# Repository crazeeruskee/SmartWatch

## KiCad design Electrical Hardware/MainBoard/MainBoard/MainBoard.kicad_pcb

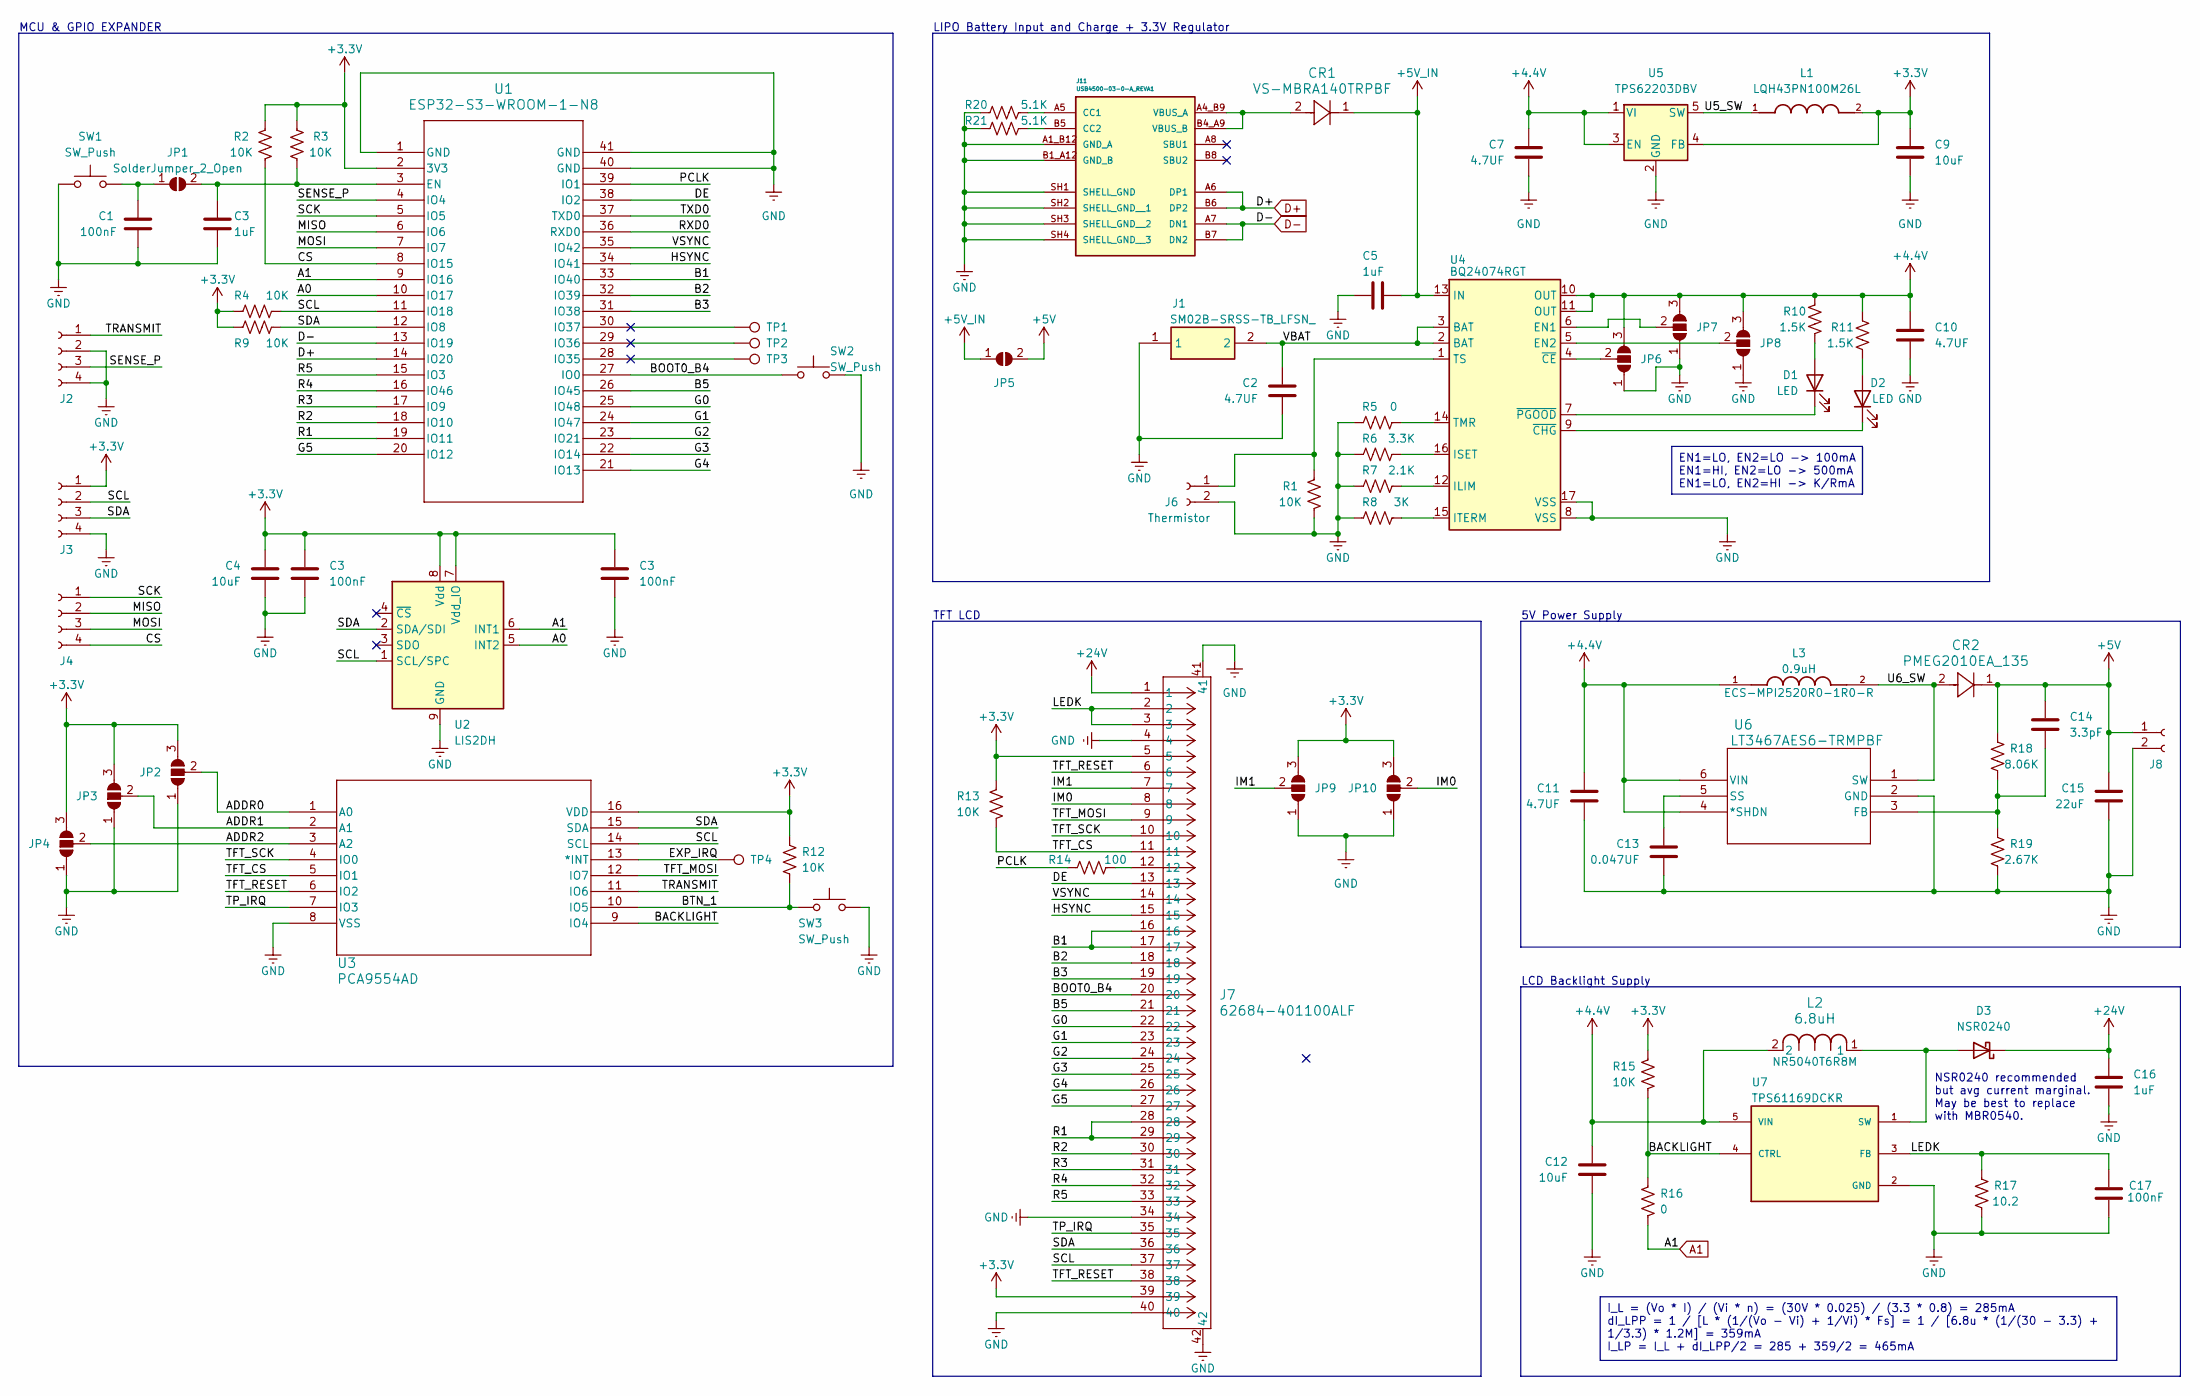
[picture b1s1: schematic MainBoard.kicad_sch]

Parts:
C1, C17: 100nF; C_0603_1608Metric
C2, C7, C10, C11: 4.7UF; C_0603_1608Metric
C3, C5, C16: 1uF; C_0603_1608Metric
C4, C9, C12: 10uF; C_0805_2012Metric
C13: 0.047UF; C_0603_1608Metric
C14: 3.3pF; C_0603_1608Metric
C15: 22uF; C_0805_2012Metric
CR1: VS-MBRA140TRPBF; DIODE_SMA_VIS-L
CR2: PMEG2010EA_135; CR_PMEG2010_NEX
D1, D2: LED; LED_0603_1608Metric
D3: NSR0240; D_SOD-123
J1: SM02B-SRSS-TB_LFSN_; SM02B-SRSS-TB; Manufacturer_Part_Number SM02B-SRSS-TB(LFSN)
J2, J3, J4: Conn_01x04_Socket; PinSocket_1x04_P1.00mm_Vertical
J6: Thermistor; PinSocket_1x02_P1.00mm_Vertical
J7: 62684-401100ALF; CONN40_1100ALF_AMP
J8: Conn_01x02_Socket; PinSocket_1x02_P1.00mm_Vertical
J11: USB4500-03-0-A_REVA1; GCT_USB4500-03-0-A_REVA1; PARTREV A1
JP1, JP5: SolderJumper_2_Open; SolderJumper-2_P1.3mm_Open_RoundedPad1.0x1.5mm
JP2, JP3, JP4, JP6, JP7, JP8, JP9, JP10: SolderJumper_3_Open; SolderJumper-3_P1.3mm_Open_RoundedPad1.0x1.5mm
L1: LQH43PN100M26L; IND_LQH43PN100M26L; PARTREV N/A
L2: 6.8uH; IND_TAIYO_NR5040_TAY; MPN NR5040T6R8M
L3: 0.9uH; IND_ECS-MPI2520R0-1R0-R; PARTREV B
R1, R2, R3, R4, R9, R12, R13, R15: 10K; R_0603_1608Metric
R5, R16: 0; R_0603_1608Metric
R6: 3.3K; R_0603_1608Metric
R7: 2.1K; R_0603_1608Metric
R8: 3K; R_0603_1608Metric
R10, R11: 1.5K; R_0603_1608Metric
R14: 100; R_0603_1608Metric
R17: 10.2; R_0603_1608Metric
R18: 8.06K; R_0603_1608Metric
R19: 2.67K; R_0603_1608Metric
R20, R21: 5.1K; R_0603_1608Metric
SW1, SW2, SW3: SW_Push; Panasonic_EVQPUJ_EVQPUA
TP1, TP2, TP3, TP4: TestPoint; TestPoint_Pad_D1.0mm
U1: ESP32-S3-WROOM-1-N8; ESP32-S3-WROOM-1-N8_EXP
U2: LIS2DH; LGA-14_2x2mm_P0.35mm_LayoutBorder3x4y
U3: PCA9554AD; SOT338-1_NXP-L
U4: BQ24074RGT; VQFN-16-1EP_3x3mm_P0.5mm_EP1.6x1.6mm
U5: TPS62203DBV; SOT-23-5
U6: LT3467AES6-TRMPBF; TSOT-23_S6_LIT
U7: TPS61169DCKR; SOT65P210X110-5N; PARTREV A

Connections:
+4V4: C7.1, C10.1, C11.1, C12.1, JP6.3 (B), JP7.3 (B), JP8.3 (B), L2.2, L3.1, R10.1, R11.2, U4.10 (OUT), U4.11 (OUT), U5.1 (VI), U5.3 (EN), U6.4 (*SHDN), U6.6 (VIN), U7.5 (VIN)
+5V: C14.1, C15.1, CR2.1, J8.1, JP5.2 (B), R18.1
+5V_IN: C5.1, CR1.1, JP5.1 (A), U4.13 (IN)
+24V: C16.1, D3.1 (K), J7.1
/A0: U1.10 (IO17), U2.5 (INT2)
/ADDR0: JP2.2 (C), U3.1 (A0)
/ADDR1: JP3.2 (C), U3.2 (A1)
/ADDR2: JP4.2 (C), U3.3 (A2)
/B1: J7.16, J7.17, U1.33 (IO40)
/B2: J7.18, U1.32 (IO39)
/B3: J7.19, U1.31 (IO38)
/B5: J7.21, U1.26 (IO45)
/BACKLIGHT: R15.2, R16.1, U3.9 (IO4), U7.4 (CTRL)
/BOOT0_B4: J7.20, SW2.1, U1.27 (IO0)
/BTN_1: R12.2, SW3.1, U3.10 (IO5)
/CS: J4.4, R2.2, U1.8 (IO15)
/DE: J7.13, U1.38 (IO2)
/EXP_IRQ: TP4.1, U3.13 (*INT)
/G0: J7.22, U1.25 (IO48)
/G1: J7.23, U1.24 (IO47)
/G2: J7.24, U1.23 (IO21)
/G3: J7.25, U1.22 (IO14)
/G4: J7.26, U1.21 (IO13)
/G5: J7.27, U1.20 (IO12)
/HSYNC: J7.15, U1.34 (IO41)
/IM0: J7.8, JP10.2 (C)
/IM1: J7.7, JP9.2 (C)
/LEDK: C17.1, J7.2, J7.3, R17.1, U7.3 (FB)
/MISO: J4.2, U1.6 (IO6)
/MOSI: J4.3, U1.7 (IO7)
/PCLK: R14.2, U1.39 (IO1)
/R1: J7.28, J7.29, U1.19 (IO11)
/R2: J7.30, U1.18 (IO10)
/R3: J7.31, U1.17 (IO9)
/R4: J7.32, U1.16 (IO46)
/R5: J7.33, U1.15 (IO3)
/RXD0: U1.36 (RXD0)
/SCK: J4.1, U1.5 (IO5)
/SCL: J3.2, J7.37, R4.2, U1.11 (IO18), U2.1 (SCL/SPC), U3.14 (SCL)
/SDA: J3.3, J7.36, R9.1, U1.12 (IO8), U2.2 (SDA/SDI), U3.15 (SDA)
/SENSE_P: J2.3, U1.4 (IO4)
/TFT_CS: J7.11, R13.2, U3.5 (IO1)
/TFT_MOSI: J7.9, U3.12 (IO7)
/TFT_RESET: J7.6, J7.38, U3.6 (IO2)
/TFT_SCK: J7.10, U3.4 (IO0)
/TP_IRQ: J7.35, U3.7 (IO3)
/TRANSMIT: J2.1, U3.11 (IO6)
/TXD0: U1.37 (TXD0)
/U5_SW: L1.1, U5.5 (SW)
/U6_SW: CR2.2, L3.2, U6.1 (SW)
/VBAT: C2.1, J1.2, U4.2 (BAT), U4.3 (BAT)
/VSYNC: J7.14, U1.35 (IO42)
A1: R16.2, U1.9 (IO16), U2.6 (INT1)
D+: J11.A6 (DP1), J11.B6 (DP2), U1.14 (IO20)
D-: J11.A7 (DN1), J11.B7 (DN2), U1.13 (IO19)
GND: C1.1, C2.2, C3.2, C4.2, C5.2, C7.2, C9.2, C10.2, C11.2, C12.2, C13.2, C15.2, C16.2, C17.2, J1.1, J2.2, J2.4, J3.4, J6.2, J7.4, J7.34, J7.40, J7.41, J7.42, J8.2, J11.A1_B12 (GND_A), J11.B1_A12 (GND_B), J11.SH1 (SHELL_GND), J11.SH2 (SHELL_GND__1), J11.SH3 (SHELL_GND__2), J11.SH4 (SHELL_GND__3), JP2.1 (A), JP3.1 (A), JP4.1 (A), JP6.1 (A), JP7.1 (A), JP8.1 (A), JP9.1 (A), JP10.1 (A), R1.2, R5.1, R6.1, R7.1, R8.1, R17.2, R19.2, R20.2, R21.2, SW1.1, SW2.2, SW3.2, U1.1 (GND), U1.40 (GND), U1.41 (GND), U2.9 (GND), U2.10 (GND), U2.11 (GND), U2.12 (GND), U2.13 (GND), U2.14 (GND), U3.8 (VSS), U4.8 (VSS), U4.17 (VSS), U5.2 (GND), U6.2 (GND), U7.2 (GND); also elsewhere on the board
unnamed: D1.2 (A), R10.2
unnamed: D1.1 (K), U4.7 (~PGOOD)
unnamed: D2.2 (A), R11.1
unnamed: D2.1 (K), U4.9 (~CHG)
unnamed: D3.2 (A), L2.1, U7.1 (SW)
unnamed: J6.1, R1.1, U4.1 (TS)
unnamed: J7.12, R14.1
unnamed: J11.A5 (CC1), R20.1
unnamed: J11.B5 (CC2), R21.1
unnamed: CR1.2, J11.A4_B9 (VBUS_A), J11.B4_A9 (VBUS_B)
unnamed: C1.2, JP1.1 (A), SW1.2
unnamed: JP6.2 (C), U4.4 (~CE)
unnamed: JP7.2 (C), U4.6 (EN1)
unnamed: JP8.2 (C), U4.5 (EN2)
unnamed: R7.2, U4.12 (ILIM)
unnamed: R6.2, U4.16 (ISET)
unnamed: R8.2, U4.15 (ITERM)
unnamed: R5.2, U4.14 (TMR)
unnamed: C14.2, R18.2, R19.1, U6.3 (FB)
unnamed: C13.1, U6.5 (SS)

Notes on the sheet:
I_L = (Vo * I) / (Vi * n) = (30V * 0.025) / (3.3 * 0.8) = 285mA dI_LPP = 1 / [L * (1/(Vo - Vi) + 1/Vi) * Fs] = 1 / [6.8u * (1/(30 - 3.3) + 1/3.3) * 1.2M] = 359mA I_LP = I_L + dI_LPP/2 = 285 + 359/2 = 465mA
EN1=LO, EN2=LO -> 100mA EN1=HI, EN2=LO -> 500mA EN1=LO, EN2=HI -> K/RmA
LCD Backlight Supply
5V Power Supply
LIPO Battery Input and Charge + 3.3V Regulator
MCU & GPIO EXPANDER
TFT LCD
NSR0240 recommended but avg current marginal. May be best to replace with MBR0540.

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
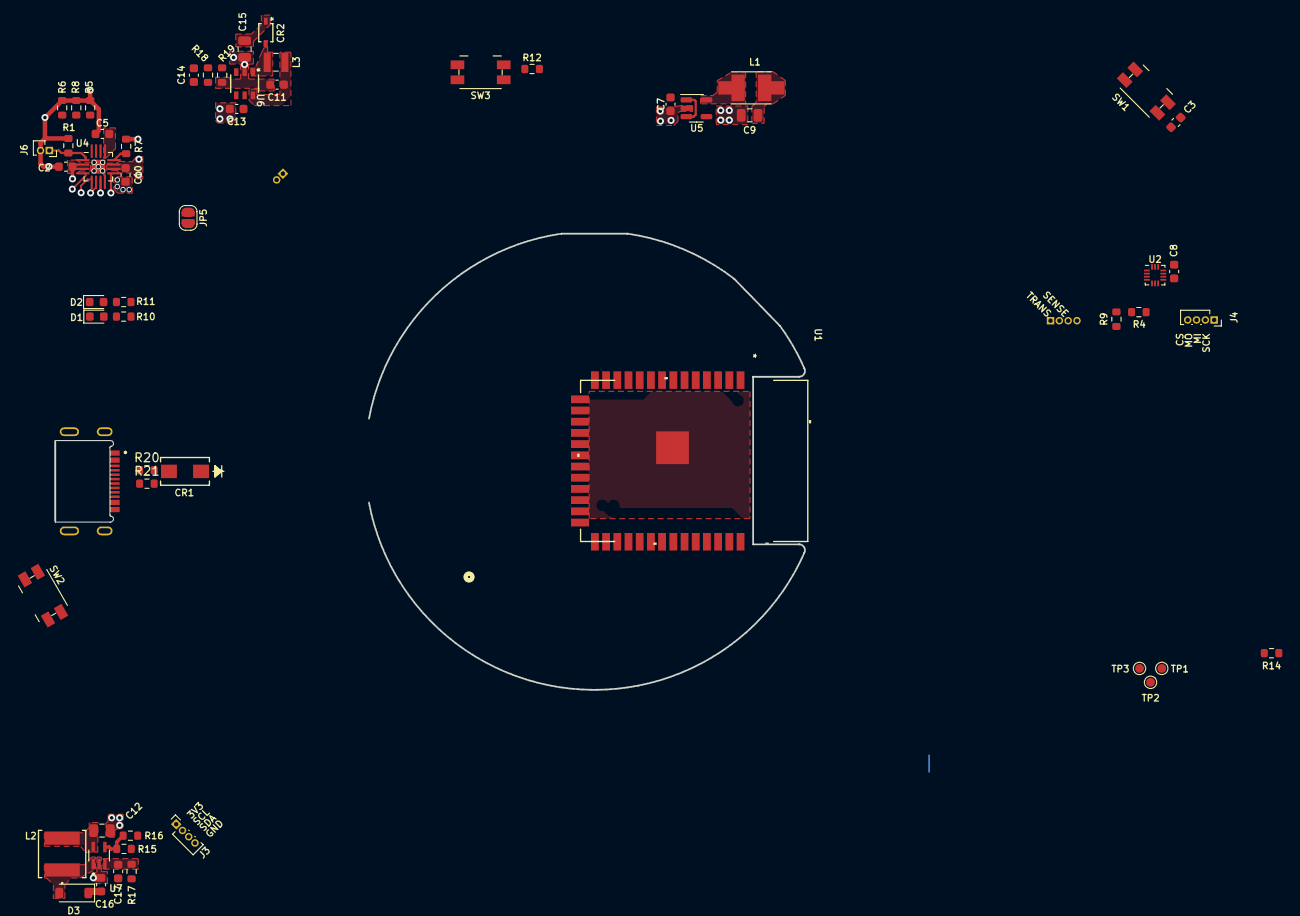
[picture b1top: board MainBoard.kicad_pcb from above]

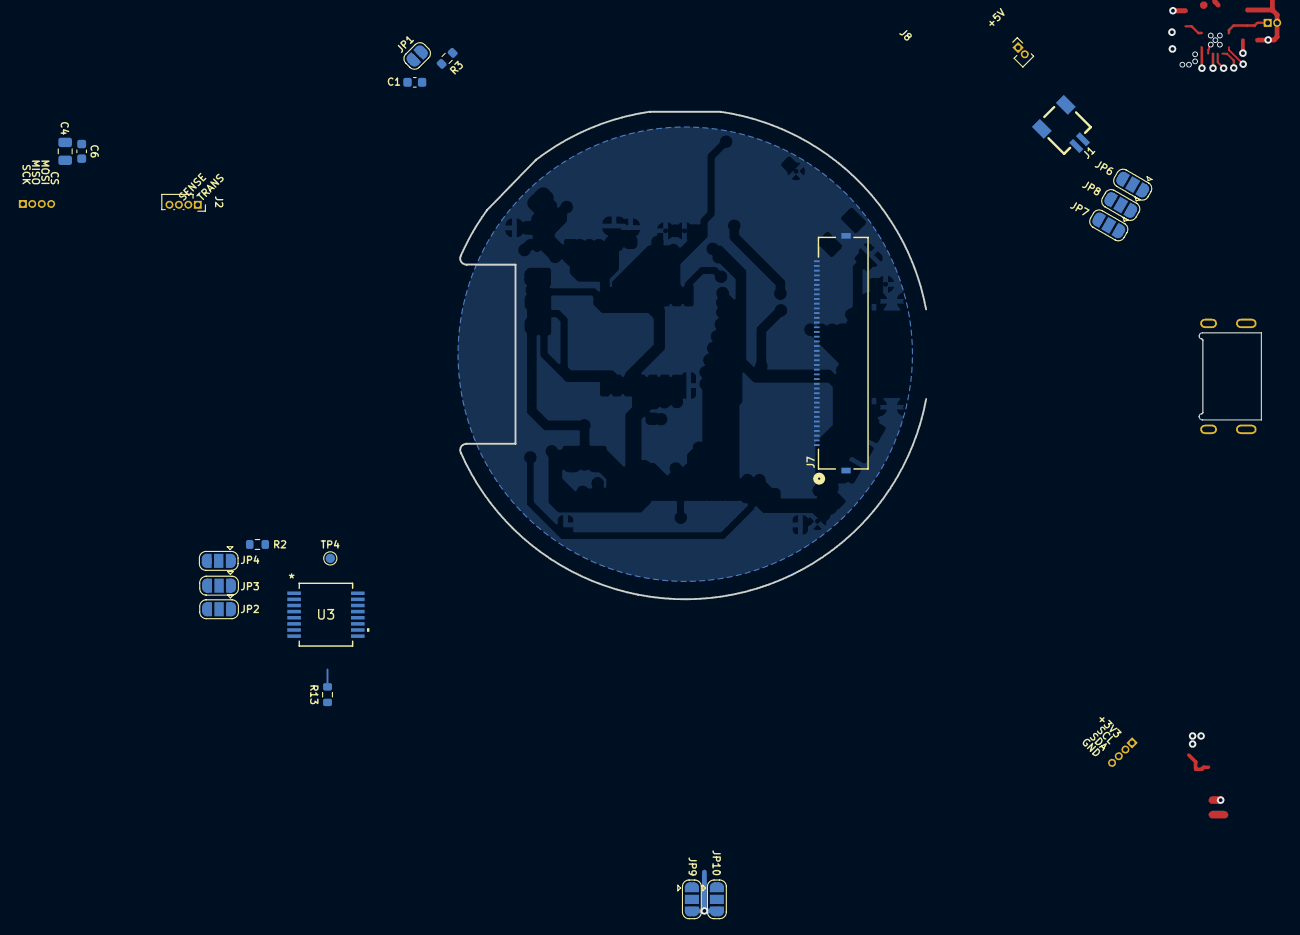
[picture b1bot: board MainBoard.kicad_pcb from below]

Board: 2 copper layers, 78 parts (21 on the bottom side), 76 nets.

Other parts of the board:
C6, C8: 100nF; C_0603_1608Metric

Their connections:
GND: C6.2, C8.2; also elsewhere on the board

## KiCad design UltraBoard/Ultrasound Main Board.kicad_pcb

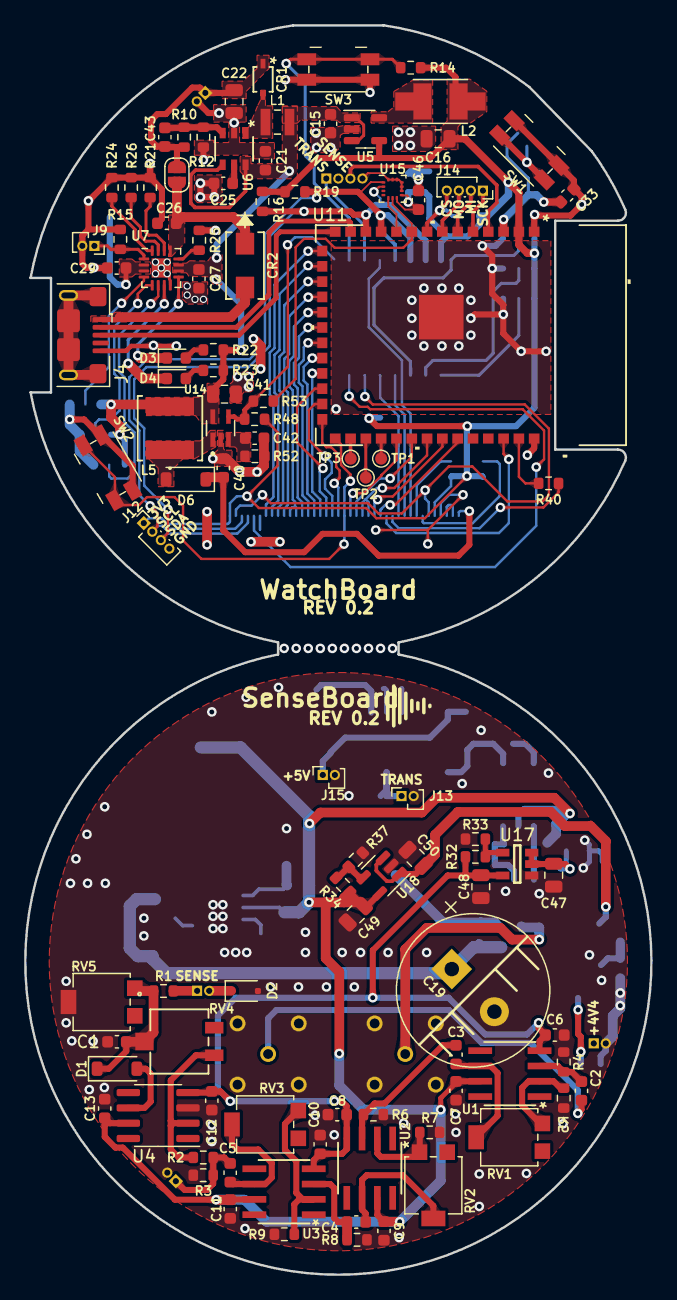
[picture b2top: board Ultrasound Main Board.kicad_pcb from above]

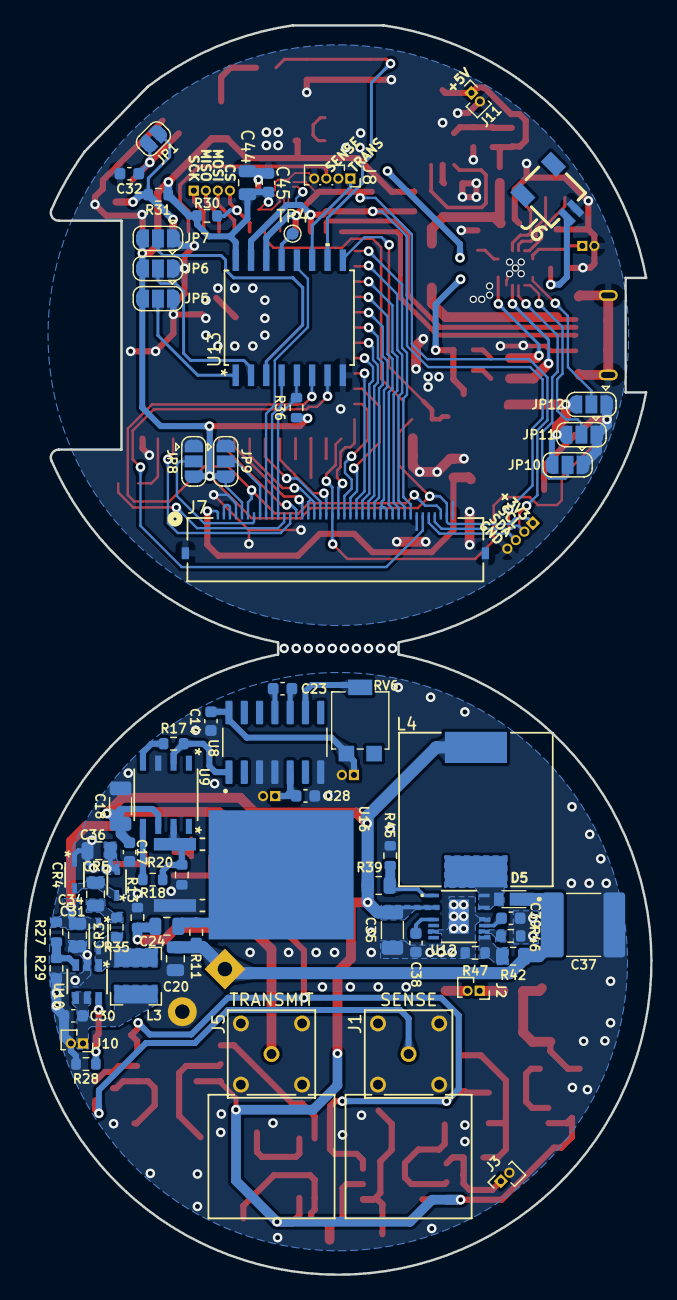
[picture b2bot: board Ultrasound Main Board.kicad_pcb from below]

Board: 2 copper layers, 52.0 x 103.7 mm, 168 parts (67 on the bottom side), 117 nets.

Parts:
C1, C2, C3, C4, C5, C28: 1nF; C_0603_1608Metric
C6, C7, C8, C9, C10, C11, C12, C13, C14, C32, C39, C42, C45, C46: 100nF; C_0603_1608Metric
C15, C21, C27, C29: 4.7UF; C_0603_1608Metric
C16, C31, C41, C44: 10uF; C_0805_2012Metric
C17: 0.1uF; C_0603_1608Metric
C18: 47uF; C_1206_3216Metric
C19: 20uF; CP_Radial_D12.5mm_P5.00mm
C20, C24: 100nF; C_0805_2012Metric
C22: 22uF; C_0805_2012Metric
C23: 50pF; C_0603_1608Metric
C25: 0.047UF; C_0603_1608Metric
C26, C30, C33, C38, C40: 1uF; C_0603_1608Metric
C34, C36, C47, C48, C49, C50: 2.2uF; C_0805_2012Metric
C35: 10uF; C_1206_3216Metric
C37: 1uF; C_2220_5650Metric
C43: 3.3pF; C_0603_1608Metric
CR1: PMEG2010EA_135; CR_PMEG2010_NEX
CR2: VS-MBRA140TRPBF; DIODE_SMA_VIS-L
CR3, CR4, CR5: CUS10S30_H3F; USC_TOS-L
D1: 1N4148W; D_SOD-123
D2: MM3Zxx; D_SOD-323F
D3, D4: LED; LED_0603_1608Metric
D5: RB558VAM150TR; TDZVTR51
D6: D_Schottky; D_SOD-123
J1, J5: EPS.00.250.NTN; CONN_EPS.00.250.NTN_LMO
J2, J3, J10, J11, J13, J15: Conn_01x02_Socket; PinSocket_1x02_P1.00mm_Vertical
J4: USB_B_Micro; USB_Micro-B_Amphenol_10118193-0001LF_Horizontal
J6: SM02B-SRSS-TB_LFSN_; SM02B-SRSS-TB
J7: 62684-401100ALF; CONN40_1100ALF_AMP
J8, J12, J14: Conn_01x04_Socket; PinSocket_1x04_P1.00mm_Vertical
J9: Thermistor; PinSocket_1x02_P1.00mm_Vertical
JP1, JP13: SolderJumper_2_Open; SolderJumper-2_P1.3mm_Open_RoundedPad1.0x1.5mm
JP5, JP6, JP7, JP8, JP9, JP10, JP11, JP12: SolderJumper_3_Open; SolderJumper-3_P1.3mm_Open_RoundedPad1.0x1.5mm
L1: 0.9uH; IND_ECS-MPI2520R0-1R0-R
L2: LQH43PN100M26L; IND_LQH43PN100M26L
L3: 4.7uH; L_Bourns-SRN4018
L4: 7447706101; IND_WE-PD_1260_WRE-L
L5: 6.8uH; IND_TAIYO_NR5040_TAY
R1, R40: 100; R_0603_1608Metric
R2, R4: 330; R_0603_1608Metric
R3, R17, R18, R21, R28, R53: 0; R_0603_1608Metric
R5: 68; R_0603_1608Metric
R6: 470; R_0603_1608Metric
R7: 820; R_0603_1608Metric
R8: 1K; R_0603_1608Metric
R9, R22, R23: 1.5K; R_0603_1608Metric
R10: 8.06K; R_0603_1608Metric
R11, R26: 3K; R_0603_1608Metric
R12: 2.67K; R_0603_1608Metric
R13: 50; R_0603_1608Metric
R14, R15, R16, R19, R20, R30, R31, R36, R48: 10K; R_0603_1608Metric
R24: 3.3K; R_0603_1608Metric
R25: 2.1K; R_0603_1608Metric
R27: 1.1M; R_0603_1608Metric
R29: 107K; R_0603_1608Metric
R32: 82K; R_0603_1608Metric
R33: 12.4K; R_0603_1608Metric
R34: 150K; R_0603_1608Metric
R35: 0.453; R_0603_1608Metric
R37: 24K; R_0603_1608Metric
R39, R42: 1M; R_0805_2012Metric
R45: 287K; R_0603_1608Metric
R46: 154K; R_0603_1608Metric
R47: 16.2K; R_0603_1608Metric
R52: 10.2; R_0603_1608Metric
RV1, RV2, RV3, RV5, RV6: 10K; Potentiometer_Bourns_3314G_Vertical
RV4: 100K; SOT_23BR100KLFTR
SW1, SW2, SW3: SW_Push; Panasonic_EVQPUJ_EVQPUA
TP1, TP2, TP3, TP4: TestPoint; TestPoint_Pad_D1.0mm
U1, U2, U3: AD811JRZ; R_8_ADI
U4: LM7171xIM; SOIC-8_3.9x4.9mm_P1.27mm
U5: TPS62203DBV; SOT-23-5
U6: LT3467AES6-TRMPBF; TSOT-23_S6_LIT
U7: BQ24074RGT; VQFN-16-1EP_3x3mm_P0.5mm_EP1.6x1.6mm
U8: 74LS121; SOIC127P600X175-14N
U9: ICL7667; SOIC8_4X5_INR-L
U10: TLV61048DBVR; SOT-23-6_DBV_TEX
U11: ESP32-S3-WROOM-1-N8; ESP32-S3-WROOM-1-N8_EXP
U12: LT8331EMSE-TRPBF; MSE_16A_ADI
U13: PCA9554AD; SOT162-1_NXP
U14: TPS61169DCKR; SOT65P210X110-5N
U15: LIS2DH; LGA-14_2x2mm_P0.35mm_LayoutBorder3x4y
U16: IRL620SPBF; D2PAK_VIS
U17: TPS72325DBVR; DBV0005A
U18: SPX3819M5-L; SOT-23-5

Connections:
+3.3V: C16.1, C44.1, C45.1, C46.1, J7.5, J7.39, J12.1, JP5.3 (B), JP6.3 (B), JP7.3 (B), JP8.3 (B), JP9.3 (B), L2.2, R14.1, R16.2, R19.1, R30.1, R31.1, R36.1, R48.1, U5.4 (FB), U11.2 (3V3), U13.16 (VDD), U15.7 (Vdd_IO), U15.8 (Vdd)
+4V4: C15.1, C21.1, C27.1, C30.1, C41.1, J10.1, JP10.3 (B), JP11.3 (B), JP12.3 (B), L1.1, L3.1, L5.2, R22.2, R23.1, U5.1 (VI), U5.3 (EN), U6.4 (*SHDN), U6.6 (VIN), U7.10 (OUT), U7.11 (OUT), U10.4 (EN), U10.5 (VIN), U14.5 (VIN)
+5V: C14.1, C22.1, C43.1, CR1.1, J11.1, J15.1, JP13.2 (B), R10.1, RV6.1, U8.14 (VCC)
+5V_IN: C26.1, CR2.1, JP13.1 (A), U7.13 (IN)
+9V: C7.1, C9.1, C11.1, C13.1, C17.1, C18.1, C35.1, C49.2, L4.1, R34.1, R39.1, U1.7 (+VS), U2.7 (+VS), U3.7 (+VS), U4.7 (V+), U9.6 (V+), U12.3 (VIN), U18.5 (OUT)
+24V: C40.1, D6.1 (K), J7.1
+100V: C19.1, C20.1, C37.1, D5.1 (K), R11.1, R42.1
-9V: C6.1, C8.1, C10.1, C12.1, C48.2, R32.1, U1.4 (-VS), U2.4 (-VS), U3.4 (-VS), U4.4 (V-), U17.5 (OUT)
/9V_S: C31.1, C50.2, CR3.1, R27.1, U18.1 (IN), U18.3 (EN)
/A0: U11.10 (IO17), U15.5 (INT2)
/ADDR0: JP5.2 (C), U13.1 (A0)
/ADDR1: JP6.2 (C), U13.2 (A1)
/ADDR2: JP7.2 (C), U13.3 (A2)
/B1: J7.16, J7.17, U11.33 (IO40)
/B2: J7.18, U11.32 (IO39)
/B3: J7.19, U11.31 (IO38)
/B5: J7.21, U11.26 (IO45)
/BACKLIGHT: R48.2, R53.1, U13.9 (IO4), U14.4 (CTRL)
/BOOT0_B4: J7.20, SW2.1, U11.27 (IO0)
/BTN_1: R14.2, SW3.1, U13.10 (IO5)
/CS: J14.4, R30.2, U11.8 (IO15)
/DE: J7.13, U11.38 (IO2)
/EXP_IRQ: TP4.1, U13.13 (*INT)
/G0: J7.22, U11.25 (IO48)
/G1: J7.23, U11.24 (IO47)
/G2: J7.24, U11.23 (IO21)
/G3: J7.25, U11.22 (IO14)
/G4: J7.26, U11.21 (IO13)
/G5: J7.27, U11.20 (IO12)
/HSYNC: J7.15, U11.34 (IO41)
/IM0: J7.8, JP9.2 (C)
/IM1: J7.7, JP8.2 (C)
/LEDK: J7.2, J7.3
/MISO: J14.2, U11.6 (IO6)
/MOSI: J14.3, U11.7 (IO7)
/PCLK: R40.2, U11.39 (IO1)
/PIEZO_I: C24.2, J5.1, R13.1
/PIEZO_O: C2.1, J1.1
/R1: J7.28, J7.29, U11.19 (IO11)
/R2: J7.30, U11.18 (IO10)
/R3: J7.31, U11.17 (IO9)
/R4: J7.32, U11.16 (IO46)
/R5: J7.33, U11.15 (IO3)
/SCK: J14.1, U11.5 (IO5)
/SCL: J7.37, J12.2, R19.2, U11.11 (IO18), U13.14 (SCL), U15.1 (SCL/SPC)
/SDA: J7.36, J12.3, R16.1, U11.12 (IO8), U13.15 (SDA), U15.2 (SDA/SDI)
/SENSE_N: D2.1 (K), J2.2
/SENSE_P: J2.1, J8.3, R1.2, U11.4 (IO4)
/TFT_CS: J7.11, R36.2, U13.5 (IO1)
/TFT_MOSI: J7.9, U13.12 (IO7)
/TFT_RESET: J7.6, J7.38, U13.6 (IO2)
/TFT_SCK: J7.10, U13.4 (IO0)
/TP_IRQ: J7.35, U13.7 (IO3)
/TRANSMIT: C28.1, J8.1, J13.1, U8.5 (B), U13.11 (IO6)
/U5_SW: L2.1, U5.5 (SW)
/U6_SW: CR1.2, L1.2, U6.1 (SW)
/VBAT: C29.1, J6.2, U7.2 (BAT), U7.3 (BAT)
/VSYNC: J7.14, U11.35 (IO42)
A1: R53.2, U11.9 (IO16), U15.6 (INT1)
D+: J4.3 (D+), U11.14 (IO20)
D-: J4.2 (D-), U11.13 (IO19)
GND: C1.1, C6.2, C7.2, C8.2, C9.2, C10.2, C11.2, C12.2, C13.2, C14.2, C15.2, C16.2, C17.2, C18.2, C19.2, C20.2, C21.2, C22.2, C25.2, C26.2, C27.2, C28.2, C29.2, C30.2, C31.2, C32.1, C33.2, C35.2, C36.2, C37.2, C38.2, C39.1, C40.2, C41.2, C42.2, C44.2, C45.2, C46.2, C47.1, C48.1, C49.1, C50.1, CR4.1, D2.2 (A), J1.2, J1.3, J1.4, J1.5, J3.2, J4.5 (GND), J4.6 (Shield), J5.2, J5.3, J5.4, J5.5, J6.1, J7.4, J7.34, J7.40, J7.41, J7.42, J8.2, J8.4, J9.2, J10.2, J11.2, J12.4, J13.2, J15.2, JP5.1 (A), JP6.1 (A), JP7.1 (A), JP8.1 (A), JP9.1 (A), JP10.1 (A), JP11.1 (A), JP12.1 (A), R3.2, R4.1, R5.1, R6.1, R7.1, R8.1, R9.1, R12.2, R13.2, R15.2, R20.2, R21.1, R24.1, R25.1, R26.1, R28.1, R29.2, R33.2, R37.2, R45.2, R46.2, R47.2, R52.2, RV5.2, SW1.1, SW2.2, SW3.2, U4.3 (+), U5.2 (GND), U6.2 (GND), U7.8 (VSS), U7.17 (VSS), U8.3 (A1), U8.4 (A2), U8.7 (GND), U9.3 (V-), U10.2 (GND), U11.1 (GND), U11.40 (GND), U11.41 (GND), U12.7 (BIAS), U12.12 (SYNC/MODE), U12.17 (PGND/GND), U13.8 (VSS), U14.2 (GND), U15.9 (GND), U15.10 (GND), U15.11 (GND), U15.12 (GND), U15.13 (GND), U15.14 (GND), U16.3 (D), U17.1 (GND), U18.2 (GND)
unnamed: C34.1, R35.1
unnamed: C34.2, CR4.2, CR5.1
unnamed: D1.2 (A), U4.6
unnamed: C1.2, D1.1 (K), R1.1, RV4.2, RV5.3
unnamed: D3.2 (A), R22.1
unnamed: D3.1 (K), U7.9 (~CHG)
unnamed: D4.2 (A), R23.2
unnamed: D4.1 (K), U7.7 (~PGOOD)
unnamed: D5.2 (A), L4.2, U12.14 (SW2), U12.16 (SW1)
unnamed: D6.2 (A), L5.1, U14.1 (SW)
unnamed: C5.2, J3.1, R2.2, R3.1
unnamed: CR2.2, J4.1 (VBUS)
unnamed: J7.12, R40.1
unnamed: J9.1, R15.1, U7.1 (TS)
unnamed: C32.2, JP1.1 (A), SW1.2
unnamed: C33.1, JP1.2 (B), R31.2, U11.3 (EN)
unnamed: JP10.2 (C), U7.6 (EN1)
unnamed: JP11.2 (C), U7.5 (EN2)
unnamed: JP12.2 (C), U7.4 (~CE)
unnamed: C2.2, R4.2, U1.3 (+IN)
unnamed: R5.2, RV1.3, U1.2 (-IN)
unnamed: C3.1, RV1.2, U1.6 (OUTPUT)
unnamed: C3.2, R6.2, U2.3 (+IN)
unnamed: R7.2, RV2.3, U2.2 (-IN)
unnamed: C4.1, RV2.2, U2.6 (OUTPUT)
unnamed: C4.2, R8.2, U3.3 (+IN)
unnamed: R9.2, RV3.3, U3.2 (-IN)
unnamed: C5.1, RV3.2, U3.6 (OUTPUT)
unnamed: R2.1, RV4.3, U4.2 (-)
unnamed: C43.2, R10.2, R12.1, U6.3 (FB)
unnamed: C25.1, U6.5 (SS)
unnamed: R25.2, U7.12 (ILIM)
unnamed: R24.2, U7.16 (ISET)
unnamed: R26.2, U7.15 (ITERM)
unnamed: R21.2, U7.14 (TMR)
unnamed: C23.2, U8.10 (Cext)
unnamed: RV6.2, U8.9 (Rint)
unnamed: C23.1, U8.11 (R/Cext)
unnamed: R17.1, U8.1 (~Q), U9.2 (INA)
unnamed: R17.2, U9.4 (INB)
unnamed: R18.1, U9.5 (~OUTB)
unnamed: R27.2, R29.1, U10.3 (FB)
unnamed: R28.2, U10.6 (FREQ)
unnamed: CR3.2, L3.2, R35.2, U10.1 (SW)
unnamed: R39.2, R45.1, U12.1 (EN/UVLO)
unnamed: R42.2, R47.1, U12.9 (FBX)
unnamed: C38.1, U12.5 (INTVCC)
unnamed: R46.1, U12.10 (RT)
unnamed: C39.2, U12.11 (SS)
unnamed: C42.1, R52.1, U14.3 (FB)
unnamed: R18.2, R20.1, U9.7 (~OUTA), U16.1 (G)
unnamed: C24.1, R11.2, U16.2 (S)
unnamed: C36.1, C47.2, CR5.2, U17.2 (IN), U17.3 (EN)
unnamed: R32.2, R33.1, U17.4 (FB)
unnamed: R34.2, R37.1, U18.4 (ADJ)

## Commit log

2024-07-02 Fix GFX and Touch library CMakes, add Arduino and TinyUSB libraries, break build
2024-07-03 Attempt to fix build issues; dig deeper hole
2024-07-03 Clean slate build
2024-07-04 Attempt to clean sample_project; re-install arduino library...still broken
2024-07-05 Start to add pieces of GFX library as needed
2024-07-06 Pull in pieces of Adafruit FT6206 library code
2024-07-07 Update main with touch code; mess with touch code some more
2024-07-08 Reinstall ESP IDF; Mess with GFX code; Refactor main smartwatch.cpp
2024-07-09 Start implementing i2c from scratch
2024-07-10 Add esp idf i2c driver to touch code and begin implementing it
2024-07-12 Reinstall esp-idf; mess with touch and i2c code
2024-07-13 Messing with Arduino Qualia test script, still not working tho
2024-07-16 Further mess with i2c and touch code
2024-07-17 Try to get clean build, still broken
2024-07-21 Attempt to fix cpp linker error with Extern C, not working yet
2024-07-22 Create watch base housing
2024-07-23 Change Base Housing to Use Larger 1578 Battery
2024-07-23 Shrink Base Housing Height 0.5mm
2024-07-24 Create initial female wrist strap
2024-07-25 Improve Base Housing and Create First Pass Female Wrist Strap
2024-07-26 Create first pass male wrist strap
2024-07-27 Adjust male wrist strap peg
2024-07-27 Create Thread Test Top; Adjust Base tab dimensions slightly
2024-07-29 Split pcb into separate main board and ultrasonic boards; adjust housing hardware
2024-07-29 Place all components are they were in previous (original) layout
2024-07-30 Adjust Silkscreen; Fix board violations and warnings;
2024-07-31 Expand ESP32 footprint pads
2024-08-01 Expand LIS2D and BQ24074 footprint pads
2024-08-02 LIS2d Layout
2024-08-03 Wire LEDK and adjust wiring
2024-08-03 Finish first pass LEDK wiring fix
2024-08-04 Make minor layout edits
2024-08-05 Add potential new USB C port; make minor layout edits
2024-08-07 Add another potential USB-C with simplified pinout
2024-08-08 Add yet another USB-C, this time's the charm - simplified pinout but still for comms
2024-08-12 Settle USB-C schematic update; begin USB-C layout edits
2024-08-13 Make layout edits
2024-08-14 Mess around with layout
2024-08-14 IM ABOUT TO YEET DIS BITCH
2024-08-15 YEETED THA BITCH
2024-08-16 Add smaller gpio expander footprint
2024-08-17 Make slow moves to un-yeet
